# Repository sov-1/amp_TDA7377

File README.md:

# Amplifier with audio-car amp TDA7377

This repo contains no only desing files for this amplifier but also an easy design for a coupling board that allows use the IC in any protoboard, this is under _proto_ folder wich has the gerber and .nc files for fabrication.

---

The goal it's to create a complete audio device 2.0 with audio jack - bluetooth input the cheapest way.
Following that, all is minded to be throug hole components, also using less space possible and carving circuits with a simple CNC 3018.

---

At actual stage I got the basic functions (stereo input with audio Jack and bluetooth) but it's lacking the front board with leds and control, including switchs for power.

---

Some files in this project, like CAD models (.stp files) bornier and DC jack are not free and was obtained in web research.

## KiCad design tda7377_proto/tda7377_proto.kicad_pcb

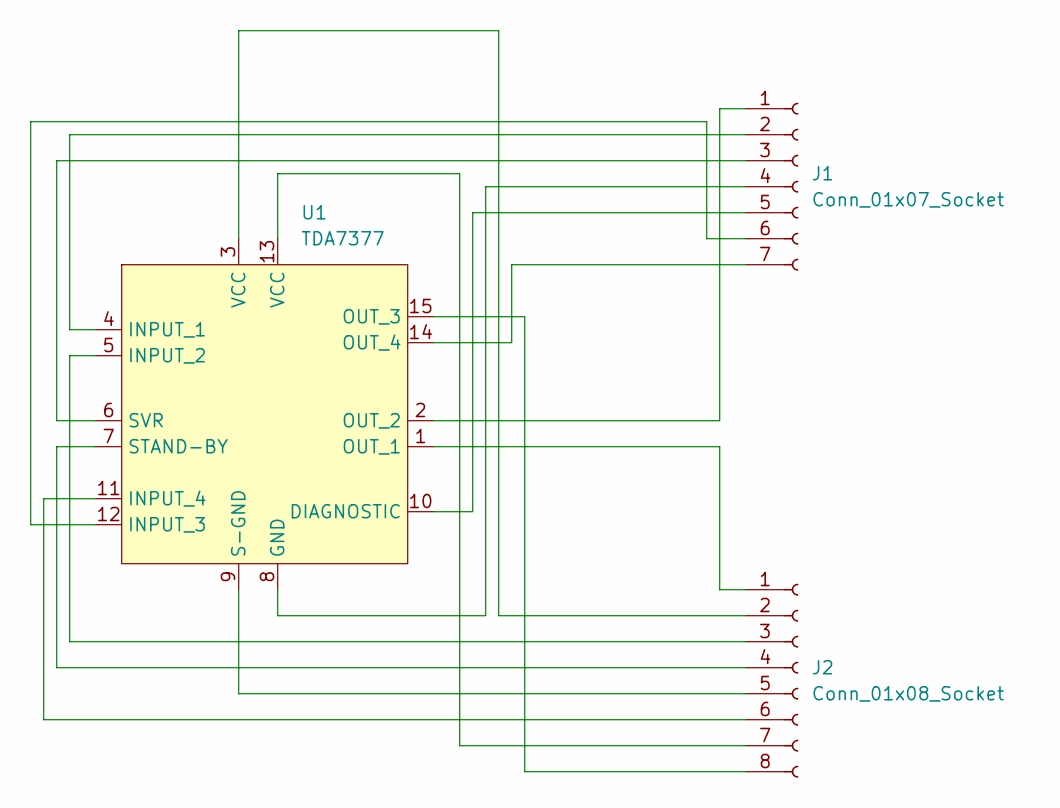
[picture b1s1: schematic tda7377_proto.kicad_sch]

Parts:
J1: Conn_01x07_Socket; PinHeader_1x07_P2.54mm_Vertical
J2: Conn_01x08_Socket; PinHeader_1x08_P2.54mm_Vertical
U1: TDA7377; TO-220-15_P2.54x2.54mm_StaggerOdd_Lead4.58mm_Vertical

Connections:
unnamed: J1.1, U1.2 (OUT_2)
unnamed: J1.2, U1.4 (INPUT_1)
unnamed: J1.3, U1.6 (SVR)
unnamed: J1.4, U1.8 (GND)
unnamed: J1.5, U1.10 (DIAGNOSTIC)
unnamed: J1.6, U1.12 (INPUT_3)
unnamed: J1.7, U1.14 (OUT_4)
unnamed: J2.1, U1.1 (OUT_1)
unnamed: J2.2, U1.3 (VCC)
unnamed: J2.3, U1.5 (INPUT_2)
unnamed: J2.4, U1.7 (STAND-BY)
unnamed: J2.5, U1.9 (S-GND)
unnamed: J2.6, U1.11 (INPUT_4)
unnamed: J2.7, U1.13 (VCC)
unnamed: J2.8, U1.15 (OUT_3)

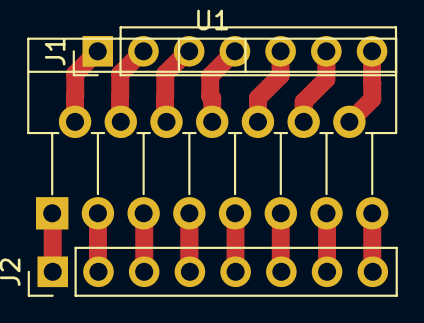
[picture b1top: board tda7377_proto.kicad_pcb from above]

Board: 2 copper layers, 3 parts (0 on the bottom side), 15 nets.

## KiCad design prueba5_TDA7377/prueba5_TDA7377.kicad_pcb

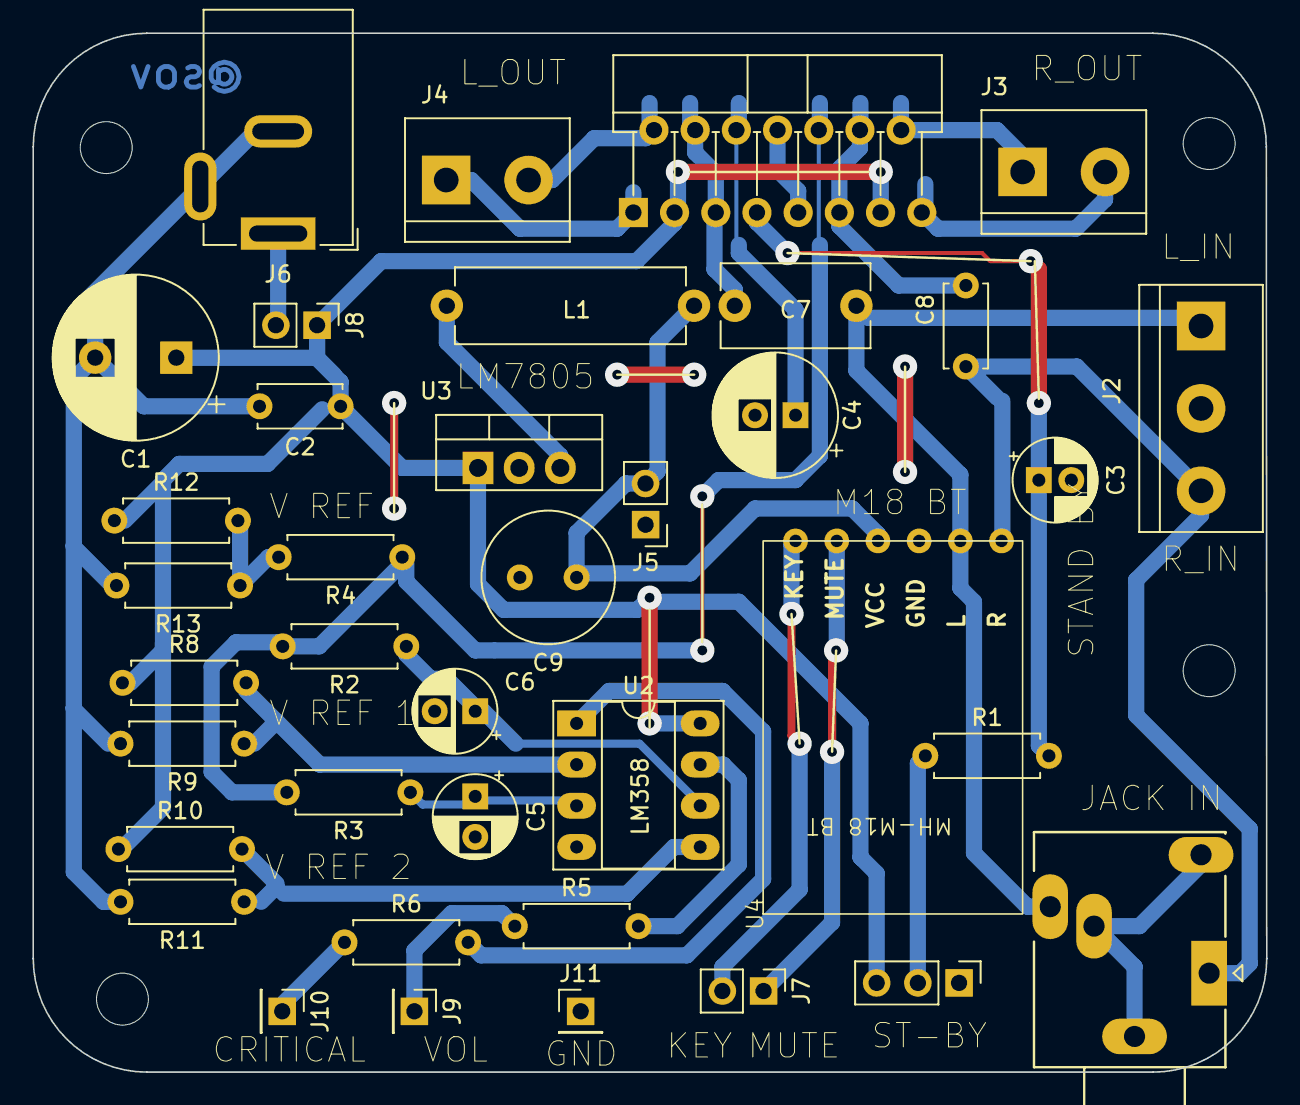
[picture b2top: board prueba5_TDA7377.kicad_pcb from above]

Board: 2 copper layers, 76.1 x 64.1 mm, 38 parts (0 on the bottom side), 28 nets.

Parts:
C1: 470 uF; CP_Radial_D10.0mm_P5.00mm
C2: 100 nF; C_Disc_D5.0mm_W2.5mm_P5.00mm
C3: 10 uF; CP_Radial_D5.0mm_P2.00mm
C4: 47 uF; CP_Radial_D7.5mm_P2.50mm
C5, C6: 10 uF; CP_Radial_D5.0mm_P2.50mm
C7: 470 nF; C_Disc_D9.0mm_W5.0mm_P7.50mm
C8: 470 nF; C_Disc_D5.0mm_W2.5mm_P5.00mm
C9: 200 uF; C_Radial_D8.0mm_H11.5mm_P3.50mm
J1: AudioJack3_Switch; Jack_3.5mm_Ledino_KB3SPRS_Horizontal
J2: Screw_T; TerminalBlock_bornier-3_P5.08mm
J3, J4: Screw_T; TerminalBlock_bornier-2_P5.08mm
J5, J7, J8: Conn_01x02_Pin; PinHeader_1x02_P2.54mm_Vertical
J6: Jack-DC; BarrelJack_GCT_DCJ200-10-A_Horizontal
J9, J10, J11: Conn_01x01_Pin; PinHeader_1x01_P2.54mm_Vertical
L1: 100 mH; L_Axial_L14.0mm_D4.5mm_P15.24mm_Horizontal_Fastron_LACC
R1: 10 k; R_Axial_DIN0207_L6.3mm_D2.5mm_P7.62mm_Horizontal
R2, R4, R10: 10k; R_Axial_DIN0207_L6.3mm_D2.5mm_P7.62mm_Horizontal
R3: 100k; R_Axial_DIN0207_L6.3mm_D2.5mm_P7.62mm_Horizontal
R5, R6: 1.2k; R_Axial_DIN0207_L6.3mm_D2.5mm_P7.62mm_Horizontal
R8: 500; R_Axial_DIN0207_L6.3mm_D2.5mm_P7.62mm_Horizontal
R9, R11, R13: 1k; R_Axial_DIN0207_L6.3mm_D2.5mm_P7.62mm_Horizontal
R12: 200; R_Axial_DIN0207_L6.3mm_D2.5mm_P7.62mm_Horizontal
ST-BY: button; PinHeader_1x03_P2.54mm_Vertical
U1: TDA7377; TO-220F-15_P2.54x5.08mm_StaggerOdd_Lead5.08mm_Vertical
U2: LM358; DIP-8_W7.62mm_Socket_LongPads
U3: LM78M05_TO220; TO-220-3_Vertical
U4: MH M18; M18

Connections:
+5V: C9.1, J5.2, L1.2, U4.3 (VCC)
DIAG: R2.2, R3.2, R4.1, U1.10 (DIAGNOSTIC)
GND: C1.2, C2.2, C3.2, C4.2, C5.2, C6.2, C9.2, J1.RN, J1.S, J1.TN, J2.2, J5.1, J6.2, J6.3, J11.1, R9.2, R11.2, R13.2, ST-BY.1 (A), U1.8 (GND), U1.9 (S-GND), U2.4 (V-), U3.2 (GND), U4.4 (GND)
LED_CRITICAL: J10.1, R6.1
LED_VOLUME: J9.1, R5.1
L_in: C7.1, J1.R, J2.1, U4.5 (L)
unnamed: J7.1, U4.2 (MUTE)
unnamed: J7.2, U4.1 (KEY)
unnamed: J6.1, J8.2
unnamed: R5.2, U2.7
unnamed: R6.2, U2.1
unnamed: R1.1, ST-BY.2 (B)
unnamed: C7.2, U1.4 (INPUT_1), U1.5 (INPUT_2)
unnamed: C8.1, U1.11 (INPUT_4), U1.12 (INPUT_3)
unnamed: C5.1, R3.1, U2.3 (+)
unnamed: C6.1, R2.1, U2.6 (-)
unnamed: L1.1, U3.3 (VO)
R_in: C8.2, J1.T, J2.3
STAND-BY: C3.1, R1.2, U1.7 (STAND-BY), U4.6 (R)
SVR: C4.1, U1.6 (SVR)
VCC: C1.1, C2.1, J8.1, R8.1, R10.1, R12.1, ST-BY.3 (C), U1.3 (VCC), U1.13 (VCC), U2.8 (V+), U3.1 (VI)
VREF: R4.2, R12.2, R13.1
VREF1: R8.2, R9.1, U2.2 (-)
VREF2: R10.2, R11.1, U2.5 (+)
out1: J4.1, U1.1 (OUT_1)
out2: J4.2, U1.2 (OUT_2)
out3: J3.2, U1.15 (OUT_3)
out4: J3.1, U1.14 (OUT_4)

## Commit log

2023-12-29 Initial project state, amp working with aux input
2023-12-29 Update basic documentation
2023-12-29 new files for documentation
2023-12-29 Update documentation
